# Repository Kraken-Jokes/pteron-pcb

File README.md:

# pteron-pcb
## Intro 

This project is the evolution of the [Pteron-Keyboard](https://github.com/FSund/pteron-keyboard) project, an incredible ergonomic keyboard that was handwired only.

I aimed to increase the appeal of this board by designing a PCB for it, and through the next months learned how to design one.

Since the case design had to be modified to fit a PCB, it was decided that this would live in a separate repository to make it easier to navigate the files and make sure that the compatible files for either version aren't mixed.

## PCB Assembly
The V2 case has a few minor alterations from the original, namely the radius around the outer case hardware and a larger radius to blend into the body to add strength to the corners. I have a weird plan for cast rubber pieces that go around the corners/ work as built in anti-slip. Not yet though.  
It also has 2 extra bolt points around the USB port. Makes the case close completely without a gap between the plates (small gap, not really noticable unless you're looking for it).

The V2 case is compatible with all Pteron56 and 60 PCBs, but it was designed to work with the USB notch in the Pteron56v0.3ul, v0.3Au, and Pteron60v0.1hsu revisions. You can check on the back of the PCB under one of the bottom outer keys for your PCB's revision.

Starting out will be the PCB build. 

I've got a quick and dirty way to bend and cut these to the right size and all you need are flush cutters and the PCB.  
Take the roll of diodes and cut them into 5 or 6 piece strips.  
Holding the board vertically, take one of the strips and hold it perpendicular to the board with the leads on a straight edge with the diode itself butted up to the top of the board.

Bend the diode legs till they're flat against the bottom of the board.  
Flip and do the same thing to the other side of the strip.

Repeat until you've bent all the legs.  

Take your snippers and cut the legs about 3-4mm below the bend. There's a perfect length to dome up on the other side without having too much to need trimming, and it's around that length. Never measured it though  

Dissasemble your pile of diodes and place them in the diode spots one by one, mark toward the square pad on the same side as the microcontroller outline. Depending on the PCB version, the diode outlines might be on that side too. 
Might not, nobody's perfect.  

Once the diodes are soldered in, tackle the Pro micro. Install the pins on the board first, solder one pin so you're able to adjust it. Test the fit to the pro micro before soldering the rest of the header pins. Once those are on, drop on the pro micro (chips TOWARD the PCB) with the micro usb connected to make sure it has clearance.

Now for the cool part. We're gonna install the Mini B connector. It goes on the same side of the microcontroller and the best way to get it connected is just to set the board on it on like a block or something, solder one of the legs then adjust if needed. Solder the other legs, then the 5 pins.  
Take the stripped micro cable and strip the 4 wires in there. Fine strippers or a high dex check and a blade are required.

Solder the cables thusly:  
Red to VBUS,  
White to D-  
Green to D+  
Black to GND  
snip the unshielded wire, or connect it to gnd idk

Plug in a mini b cable and connect it to the computer. If you're a power user, you can find all the relevant files to build the keyboard in the /firmware section.  
If you want the quick and dirty: run QMK toolbox, hit auto flash, point it to the hex file for the keyboard you're building and bridge the reset and gnd pins.

### Hotswap installation

I like doing it the slow way, so that's what I'm gonna go with. If you have a better way, by all means do what you like.  
You'll need like 6 donor switches. You might not kill them, but you might so don't use Inks if you can help it.

Take your sockets and install them on the legs of your donors.  
Insert the switches onto the PCB. The legs of the switch hold it tight to the PCB.  

Once you've got all of them on there, flip the board and solder the legs. 

I like to have the iron tip (conical) tangental to the socket contacting it and the pad, then adding solder perpendicularly into the tip. 

A little goes a long way here, add half as much as you think you'll need and you are less likely to overshoot.

Take out the switches and set aside the board for case assembly.

## case assembly

You can do the peel first, or as you install parts. I wish you a grand peeling fest!

First we'll want to take the switch plate and connect it to the PCB. This step's complexity is entirely dependant on if it's hotswap or not.  
To prevent the PCB from backing off when installing switches, each anchor point will have a connection. On soldered kits, only the 4 inner points are needed.  
Install 10mm screws into the top of the plate. Once they're through place a washer, silicone spacer, and washer onto it. Place the PCB on. Tolerances were pretty tight so you might need to push. 

Thread a washer onto each , tighten till it's the correct spacing. Check it by installing a switch.  
Don't thread a washer onto the 4 inner screws. Put a 5mm spacer there. It'll be fastened to the bottom plate. 

Install the switches in the top, then flip and solder. 

Once you have the plate/PCB assembly, set it aside. Next is the bottom case assembly.

Take the bottom plate, then install a 12mm standoff and a 5mm screw in each hole.

Install the connected stack plate, then the stack plate with a gap. 

Place the plate atop the bottom case. You may need to snap each corner in , it's fun.  
If you have a top plate, place those on top of the switch plate. Take a 10mm screw and thread a 5mm spacer all the way to the top. This centers the top plate holes.  
If you do not have a top plate, install a 5mm screw in each hole to affix it.

Flip it over and install 4 5mm screws to the middle standoffs.

### angle stands

Take 2 long pieces, and 2 of each mid piece.  
Take 4 5mm screws, then thread them into 4 12mm standoffs. Insert them into the holes, stack them long piece, two short pieces, long piece.  
Take 4 10mm screws, then thread a 5mm standoff onto the screw to the socket. you can thread those into the holes on the other side of the angle piece.  

Repeat for the other side.

Install the bumpons on the four corners, the center front, and on the front and back of each angle piece

Yay it's all together!  
Install the keycaps then enjoy the keyboard!

I hope you had a fun time building, it was a great joy (and stress) filled journey to make the PCB version of the Pteron56. I'm glad to have helped bring that amazing keyboard design to more people. 

If you have any questions or requests, feel free to drop me a line on facebook or Discord @Kraken-Jokes. 

# Old versions
**v0.1 PCB**

Congrats on getting 1 of only 5 ProtoPterons!

As it's the initial offering, there are some quirks that will differ from later versions. 

The left half of the keyboard has the diodes facing the wrong way. Just forgot to rotate those diode pads before making, so be sure to check the pads before soldering. Mark on diode goes toward the square pad.

The silkscreen layers are swapped, so the diodes will go on the opposite side of the PCB than the diode icon, and the pro micro will be soldered onto the underside of the PCB with the chip and bits facing upward toward the PCB.

The clusters of 4 diodes on the left and right side are installed on the top of the PCB. This is purely aesthetic. You can install on the underside, I just personally like it.

For the cable, there's a modified micro b USB 6" cable with the end modified to fit in the slot cut in the bottom stack plate with low clearance to fit the case. You can cut it and shorten the cable, but it's intended to just serpentine one of the standoffs to get in line with the hole. You can flip the bottom stack plate around to get the port on the other side. The modifications allow the cable to be held firmly in place by the case when it's all fit together

## Case Assembly
*note, the stack plates are no longer two piece with that horrid cut on the sides, though I never took a direct picture of the updated design*

Starting out, the case is made of stacked acrylic plates. I might look into a molded or cast case at some point, but my focus is not on that at the moment.\
Each case has 4 plates and multiple m2 hardware pieces. This creates a case with an overall height of ~16mm. You can likely only use a single 1/4" stack plate, you would just need to use 5mm or 6mm m2 standoffs instead (haven't done it though so idk)

Qty  | Item
-----|------
1x | M1.5 hex driver
1x | base (1/8")
1x | plate(1/8")
2x | stack plate (1/4")
8x | 2mm x 5mm M2 spacer
10x | 12mm M2 x 3mm standoffs
8x | 6mm M2 x 3mm standoffs
28x | 5mm M2 screws
8x | 10mm M2 screws

**Don't do the case assembly until you've soldered on diodes and the Pro Micro to the PCB**\

To start, grab the switch plate and PCB. Take 8x 10mm screws and set them through the 8 inner holes on the plate. Setting the base plate over the screws to hold them in place, flip the thing over so the screws are sticking up.\
Set a 2mm tall m2 spacer over each screw then place the PCB on top (v0.1 the text credits [pteron/pcb designed by] need to be facing the switch plate).\

Place 2x 1mm spacer on each screw. Now there's 2 spacers on either side of the PCB. Thread a 5mm standoff on each screw (there will be just enough thread)

Honestly you can install the switches before this step, but I just put them on at this point. I superglue mine in around the edge. Eventually, there will be a metal plate in this repo for removable top switches/ hotswap or some junk. Haven't got to it though. You could probably get away with not gluing them, I didn't. 

Grab the base and place a 5mm M2 screw and thread a 12mm M2 standoff on each perimeter hole.

Take the stack plates and set them onto the base. They should slide on no problem but may need to be pushed down gently. Get all the standoffs alligned before giving it the oomph though.

Now we're gonna grab the top plate assembly and overturn it onto the base plate. Install a 5mm screw in each of the 10 holes.\
The standoffs will go into the plate's perimeter holes about 1mm. This helps allignment and adds a fun build step: make sure each screw hole snaps in!
\
\
*uwu step keyboardu, your PCB barely fits!\
fufufufu, I made sure there was a .1mm offset*

Flip it over, install 8 inner 5mm M2 screws and the 5 keyboard feet. 

have fun!

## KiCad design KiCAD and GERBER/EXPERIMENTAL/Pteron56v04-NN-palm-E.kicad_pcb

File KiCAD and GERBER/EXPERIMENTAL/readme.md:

FYI, things in this realm are untested and should be treated like fever dreams of a madman until they're moved elsewhere

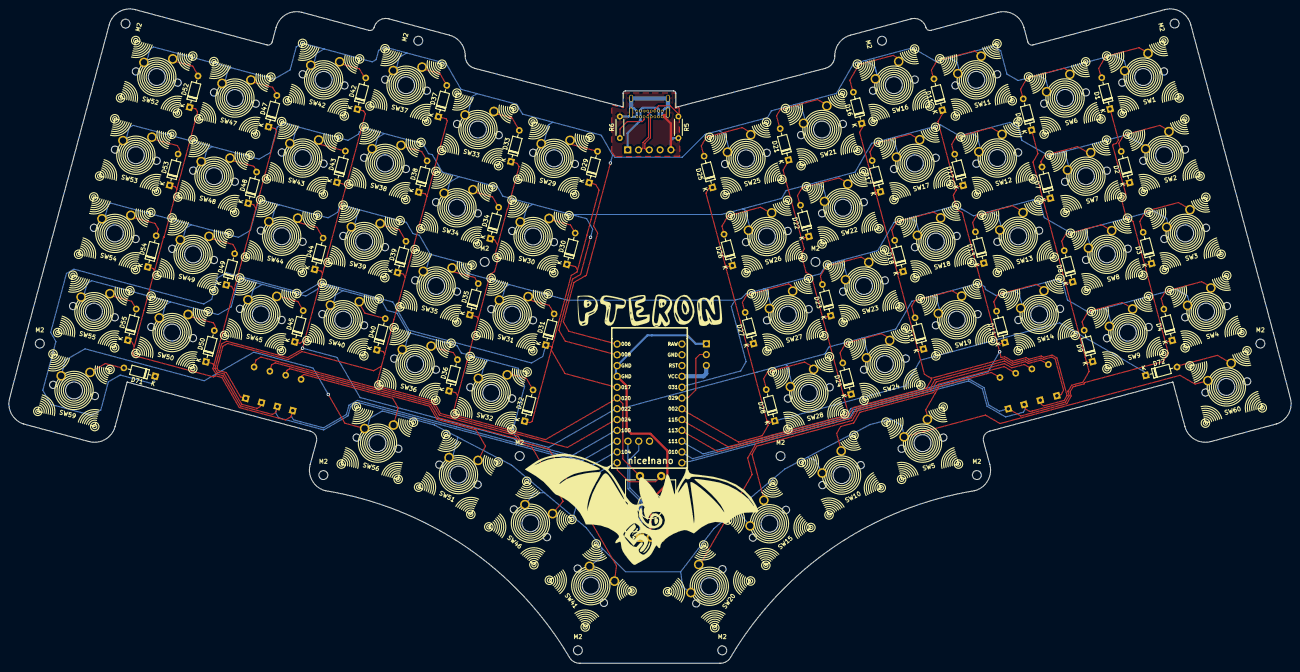
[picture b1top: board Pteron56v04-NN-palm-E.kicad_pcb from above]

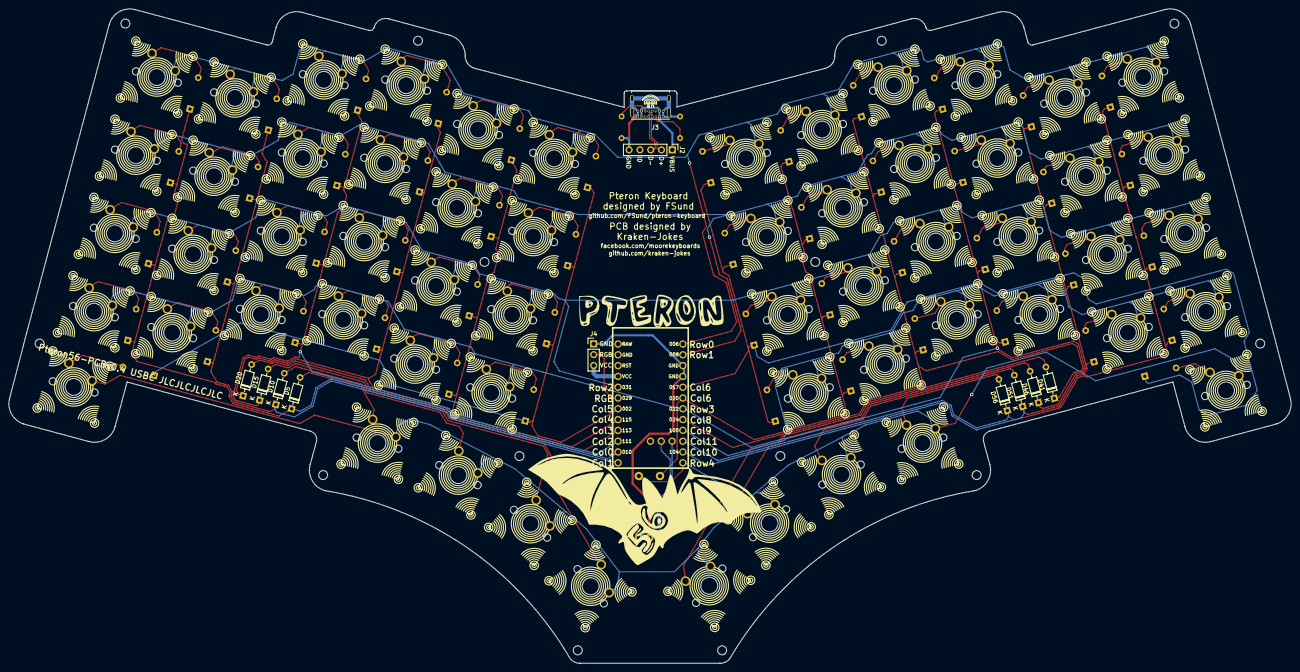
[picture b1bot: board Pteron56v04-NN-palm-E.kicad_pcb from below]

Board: 2 copper layers, 301.7 x 154.0 mm, 137 parts (11 on the bottom side), 86 nets.

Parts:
D1, D2, D3, D4, D5, D6, D7, D8, D9, D10, D11, D12, D13, D14, D15, D16, D17, D18, D19, D20, D21, D22, D23, D24, D25, D26, D27, D28, D29, D30, D31, D32, D33, D34, D35, D36, D37, D38, D39, D40, D41, D42, D43, D44, D45, D46, D47, D48, D49, D50, D51, D52, D53, D54, D55, D56, D71, D72: 1N4148; D_DO-35_SOD27_P7.62mm_Horizontal
J2: Conn_01x05_Female; USB_5POS_header
J3: USB_C_Receptacle_USB2.0; GCT_USB4085-GF-A_REVA
J4: Conn_01x03; PinHeader_1x03_P2.54mm_Vertical
M2, M2#2, M2#3, M2#4, M2#5, M2#6, M2#7, M2#8, M2#9, M2#10, M2#11, M2#12, M2#13, M2#14: MountingHole_2.1mm
R5, R6: 5.1k; R_Axial_DIN0204_L3.6mm_D1.6mm_P5.08mm_Horizontal
SW1, SW2, SW3, SW4, SW5, SW6, SW7, SW8, SW9, SW10, SW11, SW12, SW13, SW14, SW15, SW16, SW17, SW18, SW19, SW20, SW21, SW22, SW23, SW24, SW25, SW26, SW27, SW28, SW29, SW30, SW31, SW32, SW33, SW34, SW35, SW36, SW37, SW38, SW39, SW40, SW41, SW42, SW43, SW44, SW45, SW46, SW47, SW48, SW49, SW50, SW51, SW52, SW53, SW54, SW55, SW56, SW59, SW60: SW_PUSH; SW_MX_Millmax1,524
SW58: Rotary_Encoder_Switch; RotaryEncoder_EC11
U3: nice_nano

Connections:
/Col0: D1.1, D2.1, D3.1, D4.1, D5.1, U3.14
/Col1: D6.1, D7.1, D8.1, D9.1, D10.1, U3.13
/Col2: D11.1, D12.1, D13.1, D14.1, D15.1, U3.15
/Col3: D16.1, D17.1, D18.1, D19.1, D20.1, U3.16
/Col4: D21.1, D22.1, D23.1, D24.1, U3.17
/Col5: D25.1, D26.1, D27.1, D28.1, D72.1, U3.18
/Col6: D29.1, D30.1, D31.1, D32.1, D71.1, U3.5
/Col8: D37.1, D38.1, D39.1, D40.1, D41.1, U3.8
/Col9: D42.1, D43.1, D44.1, D45.1, D46.1, U3.9
/Col10: D47.1, D48.1, D49.1, D50.1, D51.1, U3.11
/Col11: D52.1, D53.1, D54.1, D55.1, D56.1, U3.10
/Row0: SW1.1, SW6.1, SW11.1, SW16.1, SW21.1, SW25.1, SW29.1, SW33.1, SW37.1, SW42.1, SW47.1, SW52.1, U3.1
/Row1: SW2.1, SW7.1, SW12.1, SW17.1, SW22.1, SW26.1, SW30.1, SW34.1, SW38.1, SW43.1, SW48.1, SW53.1, U3.2
/Row2: SW3.1, SW8.1, SW13.1, SW18.1, SW23.1, SW27.1, SW31.1, SW35.1, SW39.1, SW44.1, SW49.1, SW54.1, U3.20
/Row3: SW4.1, SW9.1, SW14.1, SW19.1, SW24.1, SW28.1, SW32.1, SW36.1, SW40.1, SW45.1, SW50.1, SW55.1, U3.7
Col7: D33.1, D34.1, D35.1, D36.1, SW58.S2, U3.6
D+: J2.2, J3.A6, J3.B6
D-: J2.3, J3.A7, J3.B7
EncA: SW58.A, U3.31
EncB: SW58.B, U3.32
GND: J4.1, SW58.C, U3.3, U3.4
unnamed: D1.2, SW1.2
unnamed: D2.2, SW2.2
unnamed: D3.2, SW3.2
unnamed: D4.2, SW4.2
unnamed: D5.2, SW5.2
unnamed: D6.2, SW6.2
unnamed: D7.2, SW7.2
unnamed: D8.2, SW8.2
unnamed: D9.2, SW9.2
unnamed: D10.2, SW10.2
unnamed: D11.2, SW11.2
unnamed: D12.2, SW12.2
unnamed: D13.2, SW13.2
unnamed: D14.2, SW14.2
unnamed: D15.2, SW15.2
unnamed: D16.2, SW16.2
unnamed: D17.2, SW17.2
unnamed: D18.2, SW18.2
unnamed: D19.2, SW19.2
unnamed: D20.2, SW20.2
unnamed: D21.2, SW21.2
unnamed: D22.2, SW22.2
unnamed: D23.2, SW23.2
unnamed: D24.2, SW24.2
unnamed: D25.2, SW25.2
unnamed: D26.2, SW26.2
unnamed: D27.2, SW27.2
unnamed: D28.2, SW28.2
unnamed: D29.2, SW29.2
unnamed: D30.2, SW30.2
unnamed: D31.2, SW31.2
unnamed: D32.2, SW32.2
unnamed: D33.2, SW33.2
unnamed: D34.2, SW34.2
unnamed: D35.2, SW35.2
unnamed: D36.2, SW36.2
unnamed: D37.2, SW37.2
unnamed: D38.2, SW38.2
unnamed: D39.2, SW39.2
unnamed: D40.2, SW40.2
unnamed: D41.2, SW41.2
unnamed: D42.2, SW42.2
unnamed: D43.2, SW43.2
unnamed: D44.2, SW44.2
unnamed: D45.2, SW45.2
unnamed: D46.2, SW46.2
unnamed: D47.2, SW47.2
unnamed: D48.2, SW48.2
unnamed: D49.2, SW49.2
unnamed: D50.2, SW50.2
unnamed: D51.2, SW51.2
unnamed: D52.2, SW52.2
unnamed: D53.2, SW53.2
unnamed: D54.2, SW54.2
unnamed: D55.2, SW55.2
unnamed: D56.2, SW56.2
unnamed: D71.2, SW59.2
unnamed: D72.2, SW60.2
unnamed: J3.A5, R6.1
unnamed: J3.B5, R5.1
RGB: J4.2, U3.19
Row4: SW5.1, SW10.1, SW15.1, SW20.1, SW41.1, SW46.1, SW51.1, SW56.1, SW58.S1, SW59.1, SW60.1, U3.12
USB0: J2.1, J3.A4, J3.A9, J3.B4, J3.B9
USBG: J2.5, J3.A1, J3.A12, J3.B1, J3.B12, J3.S1, R5.2, R6.2
VCC: J4.3, U3.21

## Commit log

2021-04-05 Firmware files
2021-04-05 Adding PCB files.
    Pteron56v0.2 fixes issues over 0.1. See changelog for deets
2021-04-05 Create changelog
2021-04-06 Images folder with images!
    Pics of the v0.1 PCB build
2021-04-06 case 2d images
    PNG of pteron56pcb_bubble case assets.svg
2021-04-06 renamed images
2021-04-06 SVG case files
    SVG case files
2021-04-06 Update changelog
    edited L9, flipped diode direction
2021-04-06 Update README.md
    Adding images and syntax/ clarity
2021-04-07 Add files via upload
    Build steps for the readme
2021-04-07 Update README.md
    Adding build images and clarity after actually piecing a kit together
2021-04-13 Update README.md
    Added PCB assy section
2021-04-14 Add files via upload
    zoom of PCB proposing proper PM placement
2021-04-15 Add files via upload
    Crappy drawing of how I intended the cable to go
2021-05-03 Angled stand and compatible stack plate
2021-05-03 Rename angle_stand.md to angle stand preview.md
2021-08-05 Rename Case files/Switch Plate.dxf to Case files/Old Version/Switch Plate.dxf
2021-08-05 Rename Case files/Stack Plate.dxf to Case files/Old Version/Stack Plate.dxf
2021-08-05 Rename Case files/Base Plate.dxf to Case files/Old Version/Base Plate.dxf
2021-08-05 Rename Case files/Pteron56pcb_bubble case assets.svg to Case files/Old Version/Pteron56pcb_bubble case assets.svg
2021-08-05 removing old version
    updated to the v0.2 with usb breakout
2021-08-07 moving to old versions
2021-08-07 Current version
2021-08-07 Updated to match current verison
2021-09-02 build steps v2 case
2021-09-03 Updated new version instructions
2021-09-22 Reuploading
2021-09-22 Pteron_60 firmware files
2021-09-22 Added .hex files for flashing
    ATMEGA 32u4 ONLY!
2021-11-24 Fixed URL for pteron keeb repo.
2021-11-28 Passthrough USB-C
    -Changed the Mini-B port to a USB-C one.
    -Aesthetic track rerouting.
    -Changed mounting hole size to 2.1mm
2021-12-03 Create EXPERIMENTAL
